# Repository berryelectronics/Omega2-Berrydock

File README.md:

# Berrydock Mini

The first one of the series, small but packs a bunch of stuff!
* Onboard Ethernet Jack with Passive PoE cabality (up to 24V)
* Onboard Lithium battery connector with 5V Booster and Charging circuit integrated
* Pinout to most of the GPIO
* Feedback to the Omega2 for when the battery is running low or when it is fully charged
* Onboard USB-to-Serial Converter (CP2102)
* Only 5x5cm in size!

Some renders of the PCB

The Schematic can also be viewed inside the project folder

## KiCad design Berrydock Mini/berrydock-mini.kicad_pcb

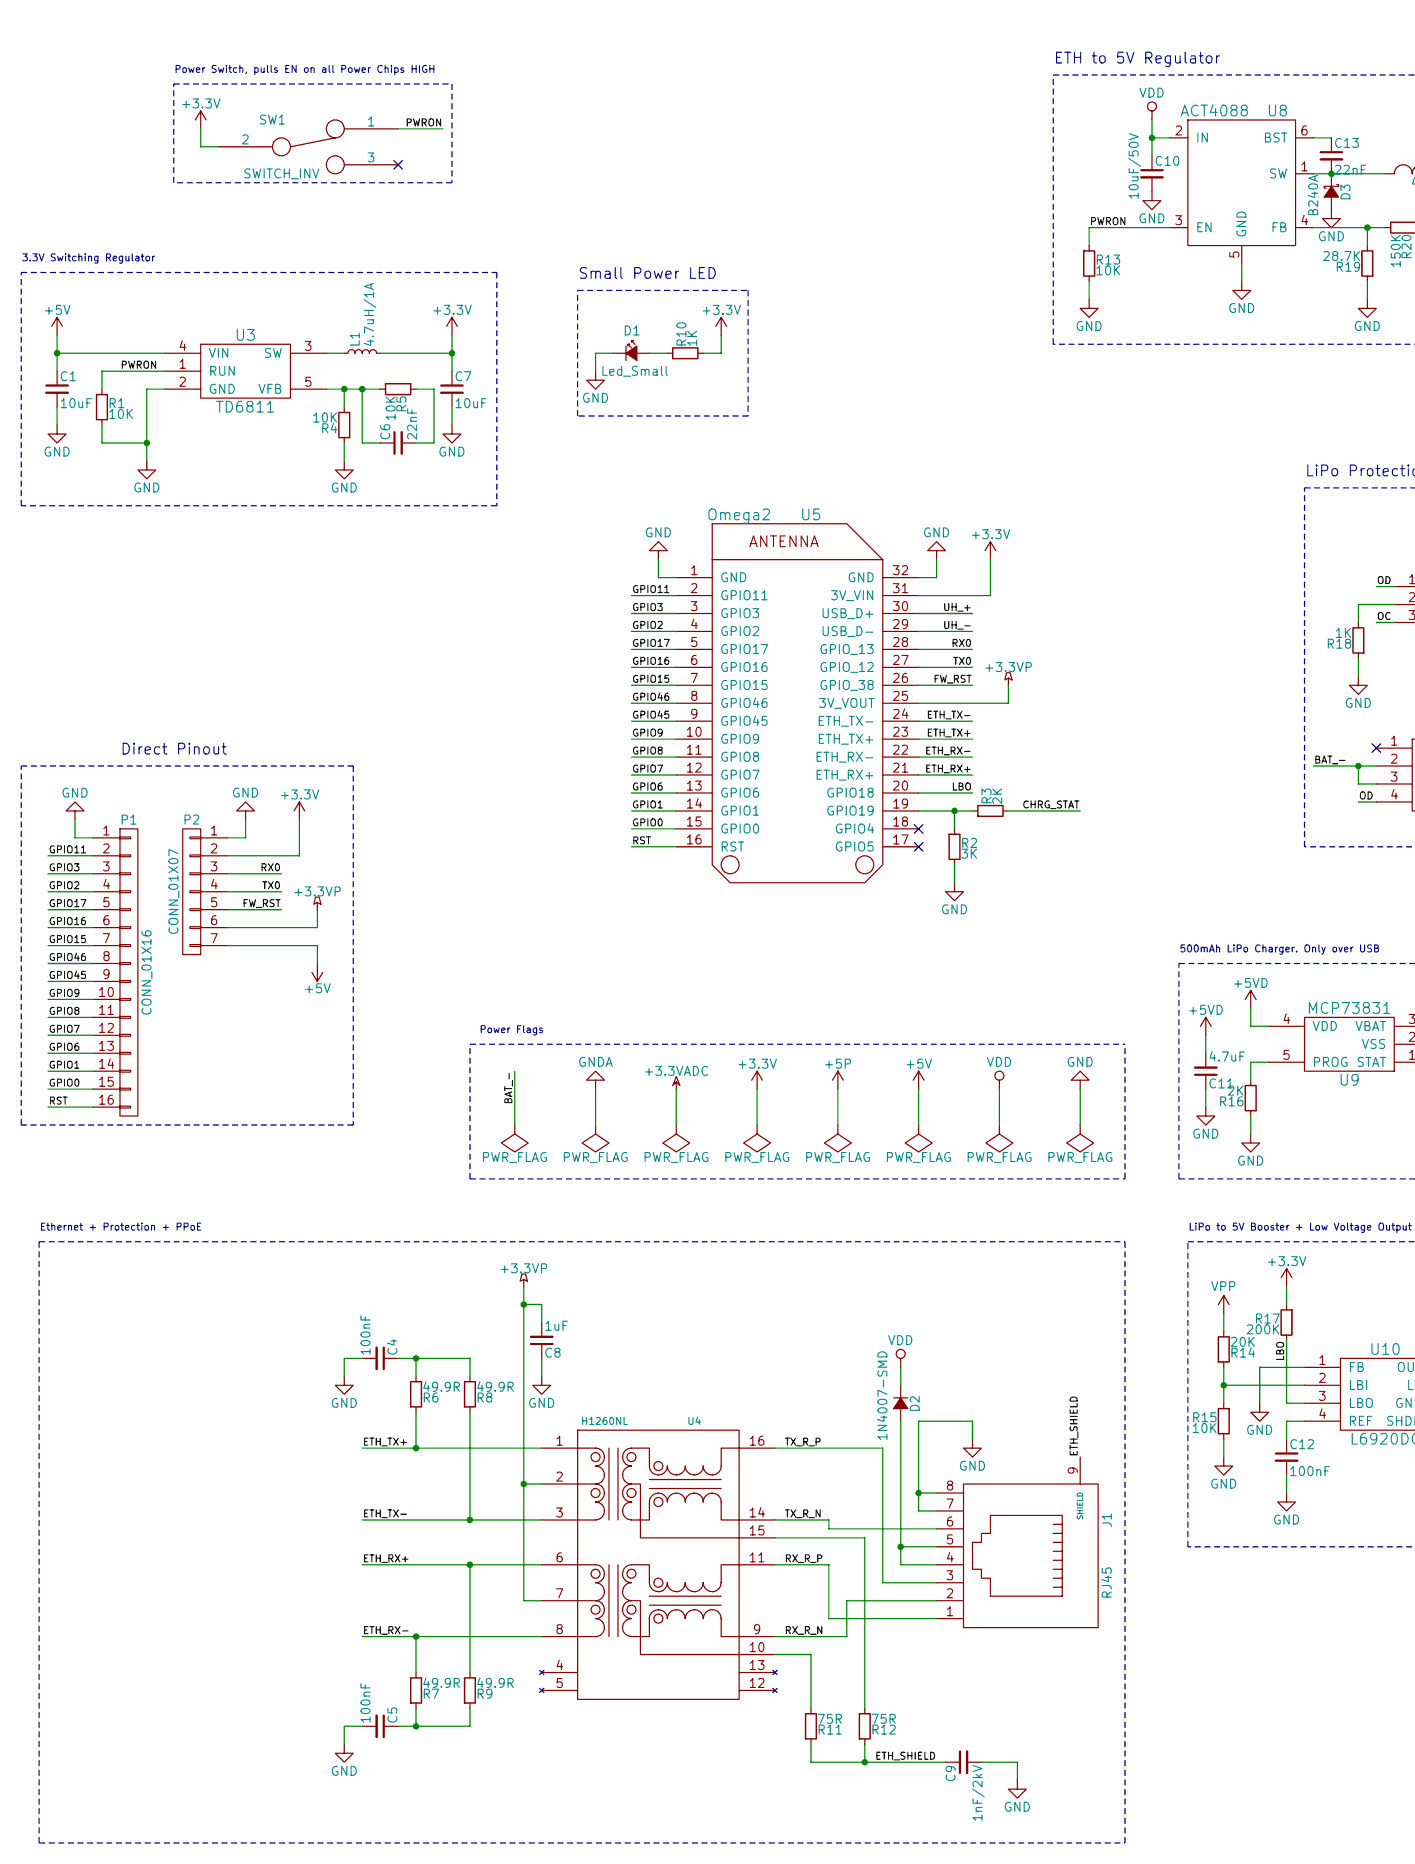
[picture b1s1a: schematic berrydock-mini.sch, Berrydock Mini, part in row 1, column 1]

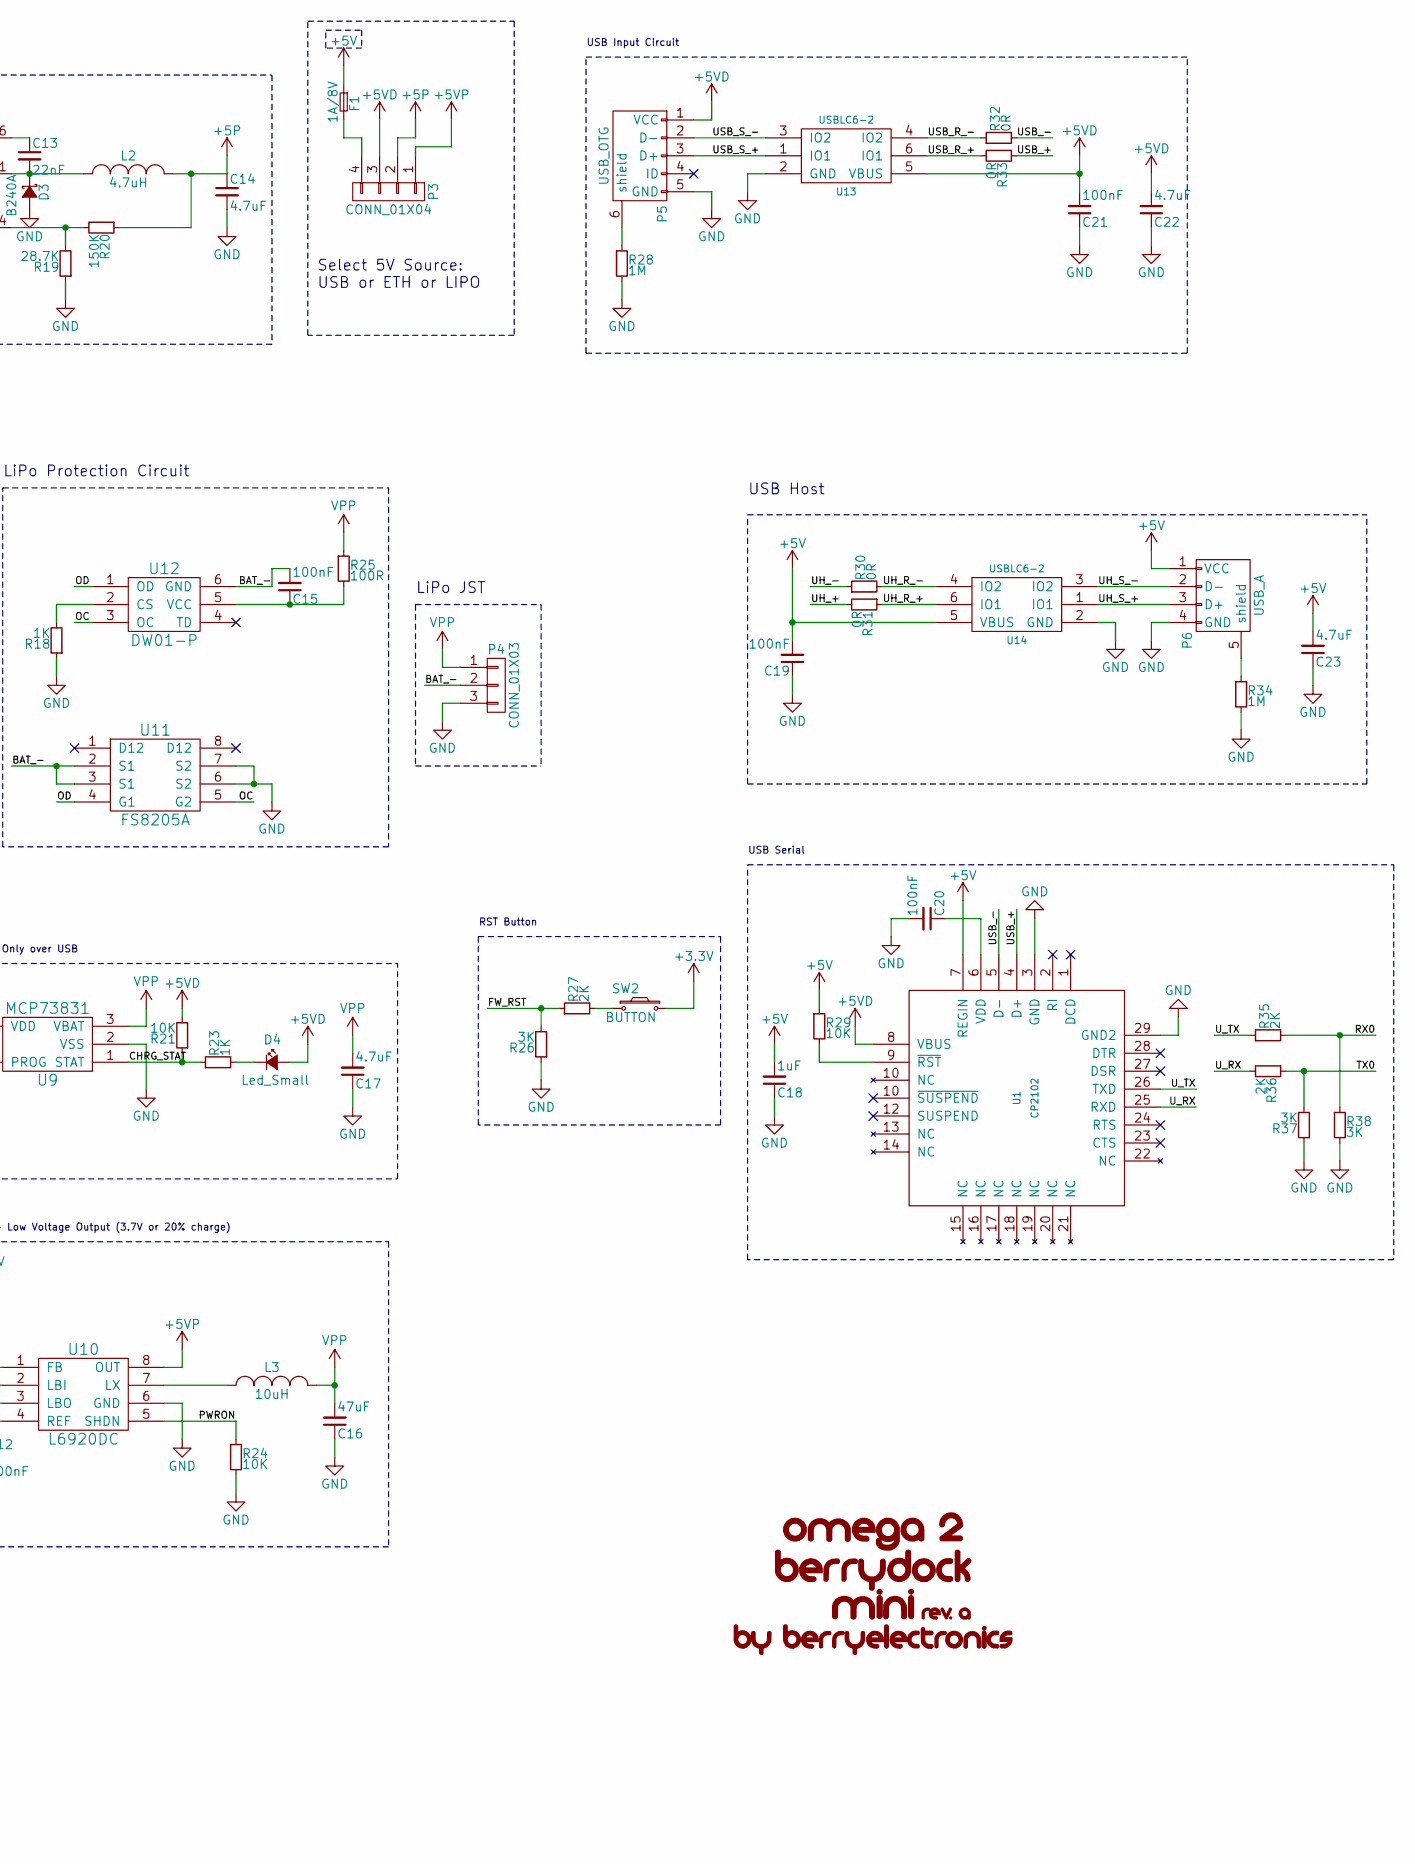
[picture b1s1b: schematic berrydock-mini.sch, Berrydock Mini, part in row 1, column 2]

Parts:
C1, C7: 10uF; C_1206
C4, C5, C12, C15, C19, C20, C21: 100nF; C_0603
C6, C13: 22nF; C_0603
C8, C18: 1uF; C_0603
C9: 1nF/2kV; C_1206
C10: 10uF/50V; C_1206
C11, C14, C17, C22, C23: 4.7uF; C_0603
C16: 47uF; C_0805
D1, D4: Led_Small; LED_0805
D2: 1N4007-SMD; DO-214AC.SMA
D3: B240A; DO-214AC.SMA
F1: 1A/8V; FUSE-1812
G1: SIMPLELOGO; simplelogo
J1: RJ45; RJ45-SHIELDED
L1: 4.7uH/1A; CD32
L2: 4.7uH; CD32
L3: 10uH; CD43
P1: CONN_01X16; Pin_Header_Straight_1x16
P2: CONN_01X07; Pin_Header_Straight_1x07
P3: CONN_01X04; PWR-SELECT
P4: CONN_01X03; JST-RIGHT-ANGLE
P5: USB_OTG; USB_Micro-B
P6: USB_A
R1, R4, R5, R13, R15, R21, R24, R29: 10K; R_0603
R2, R26, R37, R38: 3K; R_0603
R3, R16, R27, R35, R36: 2K; R_0603
R6, R7, R8, R9: 49.9R; R_0603
R10, R23: 1K; R_0603
R11, R12: 75R; R_0603
R14: 20K; R_0603
R17: 200K; R_0603
R18: 1K; R_0603_HandSoldering
R19: 28.7K; R_0603
R20: 150K; R_0603
R25: 100R; R_0603_HandSoldering
R28: 1M; R_0603
R30, R31: 0R; R_0603_HandSoldering
R32, R33: 0R; R_0603
R34: 1M; R_0603_HandSoldering
SW1: SWITCH_INV; SMD-SLIDESWITCH
SW2: BUTTON; SMD-BUTTON-2x4x3,5
U1: CP2102; QFN-28
U3: TD6811; SOT-23-5
U4: H1260NL; HL1260NL
U5: Omega2; Omega2-Outline
U8: ACT4088; SOT-23-6
U9: MCP73831; SOT-23-5
U10: L6920DC; MSOP8
U11: FS8205A; TSSOP8
U12: DW01-P; SOT-23-6_Handsoldering
U13, U14: USBLC6-2; SOT32-6L

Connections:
+3.3VP: C8.2, P2.6, U4.2, U4.7, U5.25 (3V_VOUT)
+3V3: C7.1, L1.2, P2.2, R10.2, R17.1, SW1.2, SW2.1, U5.31 (3V_VIN)
+5P: C14.1, L2.2, P3.2, R20.1
+5V: C1.1, C18.2, C19.2, C23.2, F1.1, P2.7, P6.1 (VCC), R29.1, U1.7 (REGIN), U3.4 (VIN), U14.5 (VBUS)
+5VD: C11.2, C21.2, C22.2, D4.2 (A), P3.3, P5.1 (VCC), R21.2, U1.8 (VBUS), U9.4 (VDD), U13.5 (VBUS)
+5VP: P3.1, U10.8 (OUT)
/BAT_-: C15.2, P4.2, U11.2 (S1), U11.3 (S1), U12.6 (GND)
/CHRG_STAT: R3.2, R21.1, R23.1, U9.1 (STAT)
/ETH_RX+: R9.2, U4.6, U5.21 (ETH_RX+)
/ETH_RX-: R7.2, U4.8, U5.22 (ETH_RX-)
/ETH_SHIELD: C9.1, J1.9 (SHIELD), R11.1, R12.1
/ETH_TX+: R6.1, U4.1, U5.23 (ETH_TX+)
/ETH_TX-: R8.1, U4.3, U5.24 (ETH_TX-)
/FW_RST: P2.5, R26.2, R27.1, U5.26 (GPIO_38)
/GPIO0: P1.15, U5.15 (GPIO0)
/GPIO1: P1.14, U5.14 (GPIO1)
/GPIO2: P1.4, U5.4 (GPIO2)
/GPIO3: P1.3, U5.3 (GPIO3)
/GPIO6: P1.13, U5.13 (GPIO6)
/GPIO7: P1.12, U5.12 (GPIO7)
/GPIO8: P1.11, U5.11 (GPIO8)
/GPIO9: P1.10, U5.10 (GPIO9)
/GPIO11: P1.2, U5.2 (GPIO11)
/GPIO15: P1.7, U5.7 (GPIO15)
/GPIO16: P1.6, U5.6 (GPIO16)
/GPIO17: P1.5, U5.5 (GPIO17)
/GPIO45: P1.9, U5.9 (GPIO45)
/GPIO46: P1.8, U5.8 (GPIO46)
/LBO: R17.2, U5.20 (GPIO18), U10.3 (LBO)
/OC: U11.5 (G2), U12.3 (OC)
/OD: U11.4 (G1), U12.1 (OD)
/PWRON: R1.1, R13.1, R24.1, SW1.1, U3.1 (RUN), U8.3 (EN), U10.5 (SHDN)
/RST: P1.16, U5.16 (RST)
/RX0: P2.3, R35.2, R38.1, U5.28 (GPIO_13)
/RX_R_N: J1.2, U4.9
/RX_R_P: J1.1, U4.11
/TX0: P2.4, R36.1, R37.2, U5.27 (GPIO_12)
/TX_R_N: J1.6, U4.14
/TX_R_P: J1.3, U4.16
/UH_+: R31.2, U5.30 (USB_D+)
/UH_-: R30.1, U5.29 (USB_D-)
/UH_R_+: R31.1, U14.6 (IO1)
/UH_R_-: R30.2, U14.4 (IO2)
/UH_S_+: P6.3 (D+), U14.1 (IO1)
/UH_S_-: P6.2 (D-), U14.3 (IO2)
/USB_+: R33.1, U1.4 (D+)
/USB_-: R32.2, U1.5 (D-)
/USB_R_+: R33.2, U13.6 (IO1)
/USB_R_-: R32.1, U13.4 (IO2)
/USB_S_+: P5.3 (D+), U13.1 (IO1)
/USB_S_-: P5.2 (D-), U13.3 (IO2)
/U_RX: R36.2, U1.25 (RXD)
/U_TX: R35.1, U1.26 (TXD)
GND: C1.2, C4.2, C5.2, C7.2, C8.1, C9.2, C10.2, C11.1, C12.2, C14.2, C16.1, C17.1, C18.1, C19.1, C20.2, C21.1, C22.1, C23.1, D1.1 (K), D3.2 (A), J1.7, J1.8, P1.1, P2.1, P4.3, P5.5 (GND), P6.4 (GND), R1.2, R2.2, R4.1, R13.2, R15.2, R16.1, R18.1, R19.1, R24.2, R26.1, R28.2, R34.2, R37.1, R38.2, U1.3 (GND), U1.29 (GND2), U3.2 (GND), U5.1 (GND), U5.32 (GND), U8.5 (GND), U9.2 (VSS), U10.1 (FB), U10.6 (GND), U11.6 (S2), U11.7 (S2), U13.2 (GND), U14.2 (GND)
unnamed: C4.1, R6.2, R8.2
unnamed: C5.1, R7.1, R9.1
unnamed: C6.1, R4.2, R5.2, U3.5 (VFB)
unnamed: C6.2, R5.1
unnamed: C12.1, U10.4 (REF)
unnamed: C13.1, U8.6 (BST)
unnamed: C13.2, D3.1 (K), L2.1, U8.1 (SW)
unnamed: C15.1, R25.2, U12.5 (VCC)
unnamed: C20.1, U1.6 (VDD)
unnamed: D1.2 (A), R10.1
unnamed: D2.2 (A), J1.4, J1.5
unnamed: D4.1 (K), R23.2
unnamed: F1.2, P3.4
unnamed: L1.1, U3.3 (SW)
unnamed: L3.1, U10.7 (LX)
unnamed: P5.6 (shield), R28.1
unnamed: P6.5 (shield), R34.1
unnamed: R2.1, R3.1, U5.19 (GPIO19)
unnamed: R11.2, U4.10
unnamed: R12.2, U4.15
unnamed: R14.1, R15.1, U10.2 (LBI)
unnamed: R16.2, U9.5 (PROG)
unnamed: R18.2, U12.2 (CS)
unnamed: R19.2, R20.2, U8.4 (FB)
unnamed: R27.2, SW2.2
unnamed: R29.2, U1.9 (~RST)
VDD: C10.1, D2.1 (K), U8.2 (IN)
VPP: C16.2, C17.2, L3.2, P4.1, R14.2, R25.1, U9.3 (VBAT)

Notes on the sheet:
Select 5V Source: USB or ETH or LIPO
ETH to 5V Regulator
3.3V Switching Regulator
LiPo JST
LiPo Protection Circuit
500mAh LiPo Charger. Only over USB
LiPo to 5V Booster + Low Voltage Output (3.7V or 20% charge)
USB Input Circuit
RST Button
Ethernet + Protection + PPoE
USB Host
Direct Pinout
USB Serial
Power Flags
Power Switch, pulls EN on all Power Chips HIGH
Small Power LED

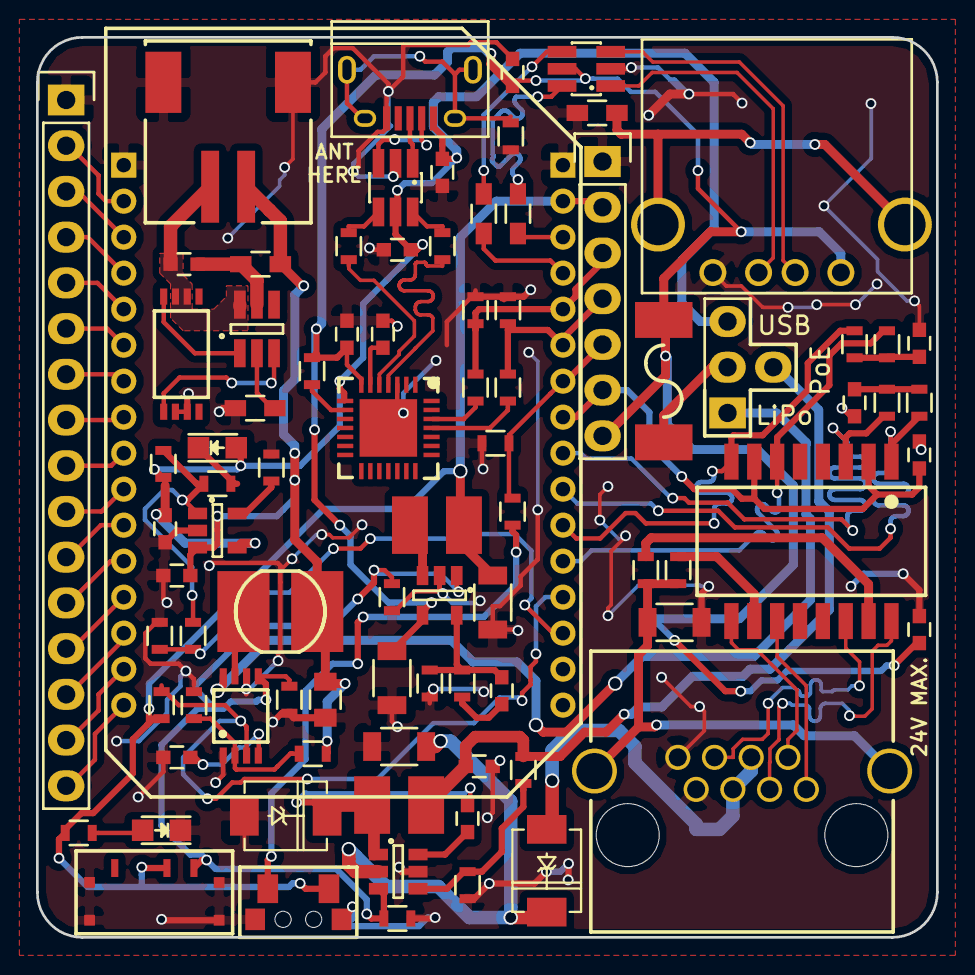
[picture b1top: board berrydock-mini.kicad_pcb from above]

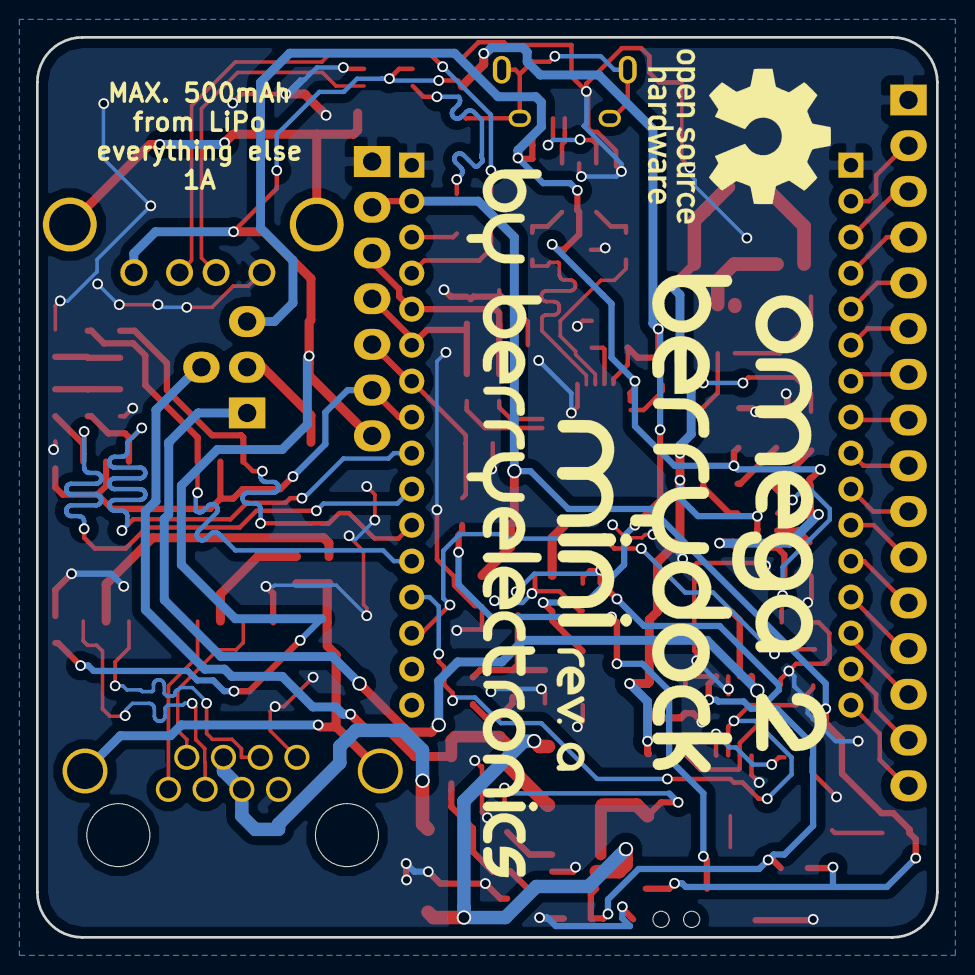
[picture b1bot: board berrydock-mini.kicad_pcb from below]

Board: 2 copper layers, 50.0 x 50.0 mm, 88 parts (2 on the bottom side), 82 nets.

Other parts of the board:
G2: OSHWLOGO; oshwlogo

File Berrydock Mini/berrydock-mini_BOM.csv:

Reference,Value,Footprint,Count,Datasheet,FootprintLib,,,,,,,
U5,Omega2,Omega2-Outline,1,,Omega2-Berrydock,,,,,,,
J1,RJ45,RJ45-SHIELDED,1,,Omega2-Berrydock,,,,,,,
C10,10uF/50V,C_1206,1,,Capacitors_SMD,,,,,,,
D3,B240A,DO-214AC.SMA,1,,Omega2-Berrydock,,,,,,,
L2,4.7uH,CD32,1,,Omega2-Berrydock,,,,,,,
U8,ACT4088,SOT-23-6_Handsoldering,1,,TO_SOT_Packages_SMD,,,,,,,
R13,R15,R29,R21,R1,R5,R4,R24,10K,R_0603_HandSoldering,8,,Resistors_SMD
C13,22nF,C_0603,1,,Capacitors_SMD,,,,,,,
R20,150K,R_0603_HandSoldering,1,,Resistors_SMD,,,,,,,
R19,28.7K,R_0603_HandSoldering,1,,Resistors_SMD,,,,,,,
C14,C11,C17,C22,C23,4.7uF,C_0603,5,,Capacitors_SMD,,,
P3,CONN_01X04,PWR-SELECT,1,,Omega2-Berrydock,,,,,,,
U12,DW01-P,SOT-23-6_Handsoldering,1,,TO_SOT_Packages_SMD,,,,,,,
U11,FS8205A,TSSOP8,1,,Omega2-Berrydock,,,,,,,
C15,C12,C21,C4,C5,C19,C20,100nF,C_0603,7,,Capacitors_SMD,
R25,100R,R_0603_HandSoldering,1,,Resistors_SMD,,,,,,,
R18,R23,R10,1K,R_0603_HandSoldering,3,,Resistors_SMD,,,,,
U9,MCP73831,SOT-23-5,1,,TO_SOT_Packages_SMD,,,,,,,
R16,R27,R36,R35,2K,R_0603_HandSoldering,4,,Resistors_SMD,,,,
D4,D1,Led_Small,LED_0805,2,,LEDs,,,,,,
U10,L6920DC,MSOP8,1,,Omega2-Berrydock,,,,,,,
L3,10uH,CD43,1,,Omega2-Berrydock,,,,,,,
R14,20K,R_0603_HandSoldering,1,,Resistors_SMD,,,,,,,
C16,47uF,C_0805,1,,Capacitors_SMD,,,,,,,
R17,200K,R_0603_HandSoldering,1,,Resistors_SMD,,,,,,,
P5,USB_OTG,USB_Micro-B,1,,Connect,,,,,,,
U13,U14,USBLC6-2,SOT32-6L,2,,Omega2-Berrydock,,,,,,
R28,R34,1M,R_0603_HandSoldering,2,,Resistors_SMD,,,,,,
F1,1A/8V,FUSE-1812,1,,Omega2-Berrydock,,,,,,,
SW1,SWITCH_INV,SMD-SLIDESWITCH,1,,Omega2-Berrydock,,,,,,,
SW2,BUTTON,"SMD-BUTTON-2x4x3,5",1,,Omega2-Berrydock,,,,,,,
R26,R37,R38,3K,R_0603_HandSoldering,3,,Resistors_SMD,,,,,
U4,H1260NL,HL1260NL,1,,Omega2-Berrydock,,,,,,,
C8,C18,1uF,C_0603,2,,Capacitors_SMD,,,,,,
R8,R6,R7,R9,49.9R,R_0603,4,,Resistors_SMD,,,,
R12,R11,75R,R_0603,2,,Resistors_SMD,,,,,,
C9,1nF/2kV,C_1206,1,,Capacitors_SMD,,,,,,,
D2,1N4007-SMD,DO-214AC.SMA,1,,Omega2-Berrydock,,,,,,,
P6,USB_A,USB_A,1,,Connect,,,,,,,
R32,R33,R30,R31,0R,R_0603_HandSoldering,4,,Resistors_SMD,,,,
U3,TD6811,SOT-23-5,1,,TO_SOT_Packages_SMD,,,,,,,
L1,4.7uH/1A,CD32,1,,Omega2-Berrydock,,,,,,,
C1,C7,10uF,C_1206,2,,Capacitors_SMD,,,,,,
P4,CONN_01X03,JST-RIGHT-ANGLE,1,,Omega2-Berrydock,,,,,,,
P1,CONN_01X16,Pin_Header_Straight_1x16,1,,Pin_Headers,,,,,,,
P2,CONN_01X07,Pin_Header_Straight_1x07,1,,Pin_Headers,,,,,,,
R3,2K,R_0603,1,,Resistors_SMD,,,,,,,
R2,3K,R_0603,1,,Resistors_SMD,,,,,,,
U1,CP2102,QFN-28,1,,Omega2-Berrydock,,,,,,,

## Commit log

2016-09-25 created mini doc project, created component library, created omega2 component
2016-09-25 created "shopping" list, created ACT4088 component
2016-09-25 added circuit for ATC4088
2016-09-25 Added AMS1118, DW01, FS8205A
2016-09-25 Added First part of power Circuit, added lipo protection circuit
2016-09-26 Added H1260NL, L6920DC, MCP73831, SMP75, USBLC6-2
2016-09-26 75% of schematic finished, power stuff all finished up.
2016-09-26 Added CP2102
2016-09-26 Added CP2102 USB Serial
2016-09-26 changed some bits here and there so that ERC test doesnt give me errors
2016-09-26 Added power flags and fixed problems for ERC
2016-09-26 Added ADS1015, ferrite bead (couldnt find one)
2016-09-26 Added ADC
2016-09-26 added layout text, added schematic PDF
2016-09-26 Connected Power Pins to GPIO for charge/low voltage on LiPo
2016-09-26 changed some resistor values
2016-09-26 added some footprints
2016-09-26 changed annontation
2016-09-27 Added Github Repo for Footprints
2016-09-27 Added many footprint
2016-09-27 Added TD6811
2016-09-27 fixed errors, new naming of items
2016-09-28 Added all footprints
2016-09-28 imported everything and laid it out
2016-09-28 First part of layout done
2016-09-29 laid everything out
2016-09-29 changes in CP2102
2016-09-29 Added DRC report file to ignore
2016-09-29 Finished Routing, only BoM and some nice graphics left to do
2016-09-29 changes in gitignore
2016-09-29 Added BoM
2016-09-29 Finished BOM Cost
2016-09-29 added ods for shopping list
2016-09-29 test generation of gerber
2016-09-30 updated schematic
2016-09-30 changed all resistor footprints to 0603, added CE8301A50P component
2016-09-30 moved all footprint descriptions to the fab layer. making pc bit more sexy
2016-09-30 added my main font
2016-09-30 changes in logo
2016-09-30 added logo psd
2016-09-30 added logo for schemati
2016-09-30 added logo bitmap
2016-09-30 final touches
2016-09-30 added OSHWLOGO
2016-09-30 OSHW Logo 10x10 Footprint
2016-09-30 OSHW Bitmap
2016-09-30 new gerbers!
2016-09-30 renamed edge layer to .gml
2016-09-30 updated gerbers
2016-09-30 updates in pcb
2016-09-30 PCB Front and Back PDF added, Schematic PDF updates
